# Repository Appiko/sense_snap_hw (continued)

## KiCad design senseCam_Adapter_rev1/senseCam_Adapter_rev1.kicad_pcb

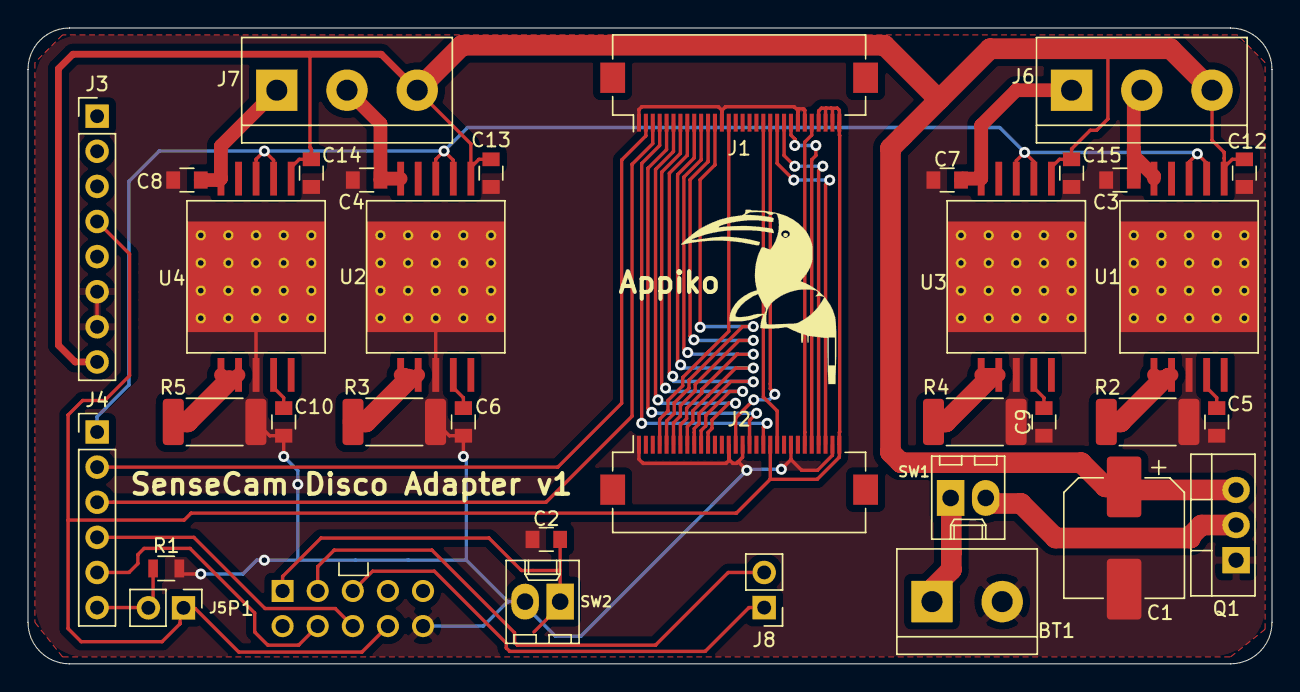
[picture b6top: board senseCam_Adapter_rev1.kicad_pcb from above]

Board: 2 copper layers, 90.0 x 46.0 mm, 36 parts (0 on the bottom side), 42 nets.

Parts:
BT1: LiPo 2s; TerminalBlock_bornier-2_P5.08mm
C1: 100uF; CP_Elec_8x10.5
C2, C12, C13, C14, C15: 100nF; C_0805
C3, C4, C7, C8: 0.47uF; C_0805
C5, C6, C9, C10: 0.1nF; C_0805
J1: Conn_01x30; ArduCam_FPC_30pin_P0.50mm_Horizontal
J2: Conn_01x30; Hirose_FH12-30S-0.5SH_1x30-1MP_P0.50mm_Horizontal
J3: Conn_01x08; PinHeader_1x08_P2.54mm_Vertical
J4: Conn_01x06; PinHeader_1x06_P2.54mm_Vertical
J5: LDR_CONN; Pin_Header_Straight_1x02_Pitch2.54mm
J6, J7: Conn_01x03; TerminalBlock_bornier-3_P5.08mm
J8: Conn_01x02; PinHeader_1x02_P2.54mm_Vertical
P1: CONN_02X05; Berg_5x2Conn
Q1: IRF9540; TO-220-3_Vertical
R1: 10k; R_0805
R2, R3, R4, R5: 0R033; R_2512_6332Metric_Pad1.52x3.35mm_HandSolder
SW1: SW_SPST; Molex_KK-6410-02_02x2.54mm_Straight
SW2: SW_Push; Molex_KK-6410-02_02x2.54mm_Straight
U1, U2, U3, U4: STCS2A; STCS2A_PowerSO-10

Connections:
/3V3: J1.27, J1.28, J1.29, J1.30, J2.20, J2.30, J3.4, J5.1, P1.8
/BUTTON: C2.1, P1.1, SW2.1
/CAM_FLASH: J1.2, J4.2
/CAM_TRIGGER: J1.3, J4.3
/Camera_CLK: J1.19, J2.21
/D4: J1.14, J2.4
/D5: J1.12, J2.5
/D6: J1.11, J2.6
/D7: J1.10, J2.7
/D8: J1.9, J2.8
/D9: J1.8, J2.9
/D10: J1.7, J2.10
/D11: J1.6, J2.11
/DCMI_HSYNC: J1.5, J2.17
/DCMI_NRST: J1.23, J2.26
/DCMI_PIXCK: J1.20, J2.15
/DCMI_PWR_EN: J1.26, J2.25
/DCMI_SCL: J1.21, J2.28
/DCMI_SDA: J1.22, J2.27
/DCMI_VSYNC: J1.4, J2.19
/FLASH_TRIGGER: J4.1, U1.2, U1.3, U2.2, U2.3, U3.2, U3.3, U4.2, U4.3
/FOCUS: J4.5, P1.4
/LDR: J4.6, J5.2, R1.1
/LED1: C3.2, J6.2, U1.5
/LED2: C7.1, J6.1, U3.5
/LED3: C4.2, J7.2, U2.5
/LED4: C8.2, J7.1, U4.5
/SENSE_TRIGGER: J4.4, P1.6
/STM_RX: J8.1, P1.5
/STM_TX: J8.2, P1.3
/VIN: C1.1, C12.1, C13.1, C14.1, C15.1, J3.8, J6.3, J7.3, Q1.3, U1.1, U2.1, U3.1, U4.1
GND: BT1.2, C1.2, C2.2, C3.1, C4.1, C5.1, C6.1, C7.2, C8.1, C9.1, C10.1, C12.2, C13.2, C14.2, C15.2, J1.1, J1.13, J1.24, J1.25, J2.1, J2.14, J2.16, J2.23, J2.29, J3.6, J3.7, P1.10, Q1.1, R1.2, R2.2, R3.2, R4.2, R5.2, SW2.2, U1.8, U1.11, U2.8, U2.11, U3.8, U3.11, U4.8, U4.11
unnamed: BT1.1, SW1.1
unnamed: C5.2, U1.9
unnamed: C6.2, U2.9
unnamed: C9.2, U3.9
unnamed: C10.2, U4.9
unnamed: Q1.2, SW1.2
unnamed: R2.1, U1.6, U1.7
unnamed: R3.1, U2.6, U2.7
unnamed: R4.1, U3.6, U3.7
unnamed: R5.1, U4.6, U4.7

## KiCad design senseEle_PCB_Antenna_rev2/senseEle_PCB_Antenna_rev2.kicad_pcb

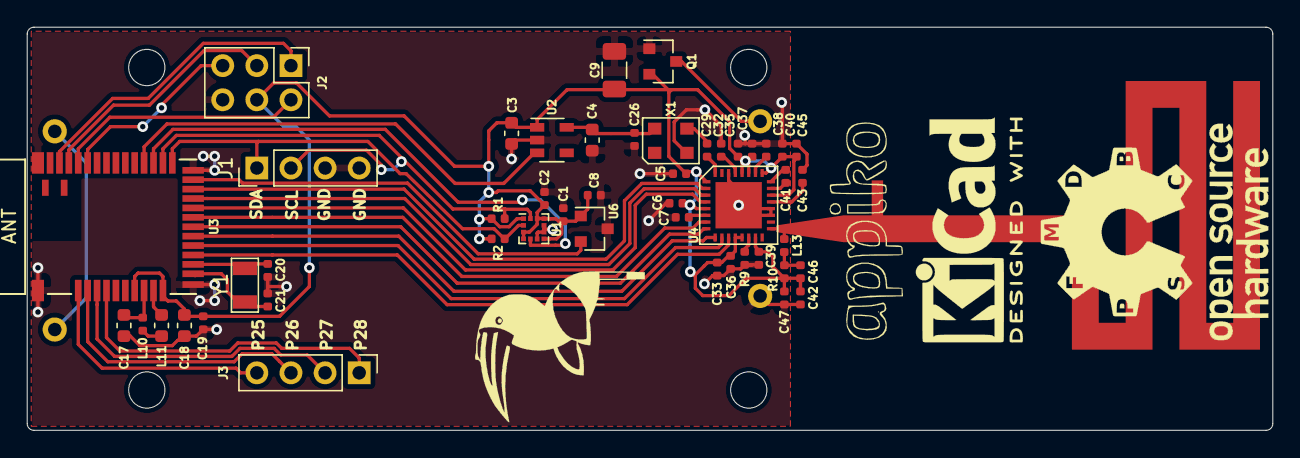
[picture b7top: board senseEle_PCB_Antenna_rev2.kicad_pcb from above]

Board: 2 copper layers, 92.7 x 30.0 mm, 54 parts (1 on the bottom side), 42 nets.

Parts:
AE1: Antenna; DN024_taper
BT1: MP000325
C1, C2, C8, C19, C26: 100nF; C_0402_1005Metric
C3, C4, C17, C18: 1uF; C_0603_1608Metric
C5, C6, C32, C33, C35, C36, C37, C38, C39, C40, C45: 47nF; C_0402_1005Metric
C7: 220nF; C_0402_1005Metric
C9: 22uF; C_1206_3216Metric
C20, C21: 8pF; C_0402_1005Metric
C29: 22pF; C_0402_1005Metric
C41: 1.8nF; C_0402_1005Metric
C42, C43: 10nF; C_0402_1005Metric
C46: 33pF; C_0402_1005Metric
C47: 100pF; C_0402_1005Metric
J1: Conn_01x02; PinHeader_1x04_P2.54mm_Vertical
J2: Conn_02x03_Odd_Even; PinHeader_2x03_P2.54mm_Vertical
J3: Conn_01x04; PinHeader_1x04_P2.54mm_Vertical
L10: 15nH; C_0402_1005Metric
L11: 10uH; C_0603_1608Metric
L13: 10nH; C_0402_1005Metric
MK1, MK2, MK3, MK4: Mounting_Hole; MountingHole_2.7mm_M2.5
Q1: IRLML6401; SOT-23
R1, R2: 10k; C_0402_1005Metric
R9: 56k; C_0402_1005Metric
R10: 10E; C_0402_1005Metric
U1: KXTJ3-1057; LGA-12_2x2mm_P0.5mm
U2: MIC5504-1.8YM5; SOT-23-5
U3: MDBT42Q; mdbt42Q
U4: CC1175; CC1120
U6: SI7201-B-00-FV; SOT-23
X1: TXKTPCSANF-32
Y1: Crystal; Q13FC1350000400_SMD_Crystals

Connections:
/CC1120/1V8: C4.2, C26.2, U2.5, X1.4
/CC1120/CSN: U3.15, U4.11
/CC1120/GPIO0: U3.16, U4.10
/CC1120/GPIO2: U3.20, U4.4
/CC1120/GPIO3: U3.21, U4.3
/CC1120/MISO: U3.17, U4.9
/CC1120/MOSI: U3.19, U4.7
/CC1120/RESET_N: U3.22, U4.2
/CC1120/SCLK: U3.18, U4.8
/CC1120/TCXO_EN: U2.3, U3.28
/nRF_Module/DCC: L11.2, U3.10
/nRF_Module/DEC4: C17.1, L10.1, U3.9
/nRF_Module/HallEffect: U3.23, U6.2
/nRF_Module/INT: U1.5, U3.27
/nRF_Module/RX: J2.2, U3.35
/nRF_Module/SCL: J1.2, R1.2, U1.12, U3.26
/nRF_Module/SDA: J1.1, R2.2, U1.2, U3.25
/nRF_Module/SWDCLK: J2.3, U3.36
/nRF_Module/SWDIO: J2.1, U3.37
/nRF_Module/TX: J2.5, U3.34
/nRF_Module/XL1: C20.1, U3.13, Y1.1
/nRF_Module/XL2: C21.1, U3.14, Y1.2
GND: BT1.2, C1.2, C2.2, C3.1, C4.1, C5.1, C6.1, C7.1, C8.2, C9.2, C17.2, C18.2, C19.2, C20.2, C21.2, C26.1, C32.2, C33.1, C35.2, C36.1, C37.2, C38.2, C39.1, C40.2, C42.1, C43.1, C45.1, C47.1, J1.3, J1.4, J2.6, Q1.1, R9.2, U1.6, U1.8, U1.9, U2.2, U3.1, U3.12, U3.24, U3.39, U4.19, U4.20, U4.30, U4.33, U6.3, X1.2
unnamed: AE1.1, L13.1, U4.17
unnamed: BT1.1, BT1.4
unnamed: BT1.3, Q1.3
unnamed: C7.2, U4.6
unnamed: C29.1, U4.32
unnamed: C29.2, X1.3
unnamed: C32.1, U4.29
unnamed: C38.1, U4.26
unnamed: C41.1, U4.23
unnamed: C41.2, U4.24
unnamed: C43.2, U4.21
unnamed: C46.2, L13.2, R10.1
unnamed: J3.1, U3.5
unnamed: J3.2, U3.4
unnamed: J3.3, U3.3
unnamed: J3.4, U3.2
unnamed: L10.2, L11.1
unnamed: R9.1, U4.14
VDD: C1.1, C2.1, C3.2, C5.2, C6.2, C8.1, C9.1, C18.1, C19.1, C33.2, C35.1, C36.2, C37.1, C39.2, C40.1, C42.2, C45.2, C46.1, C47.2, J2.4, Q1.2, R1.1, R2.1, R10.2, U1.1, U1.3, U1.4, U1.7, U1.10, U1.11, U2.1, U3.8, U3.11, U4.1, U4.5, U4.12, U4.13, U4.15, U4.22, U4.25, U4.27, U4.28, U6.1

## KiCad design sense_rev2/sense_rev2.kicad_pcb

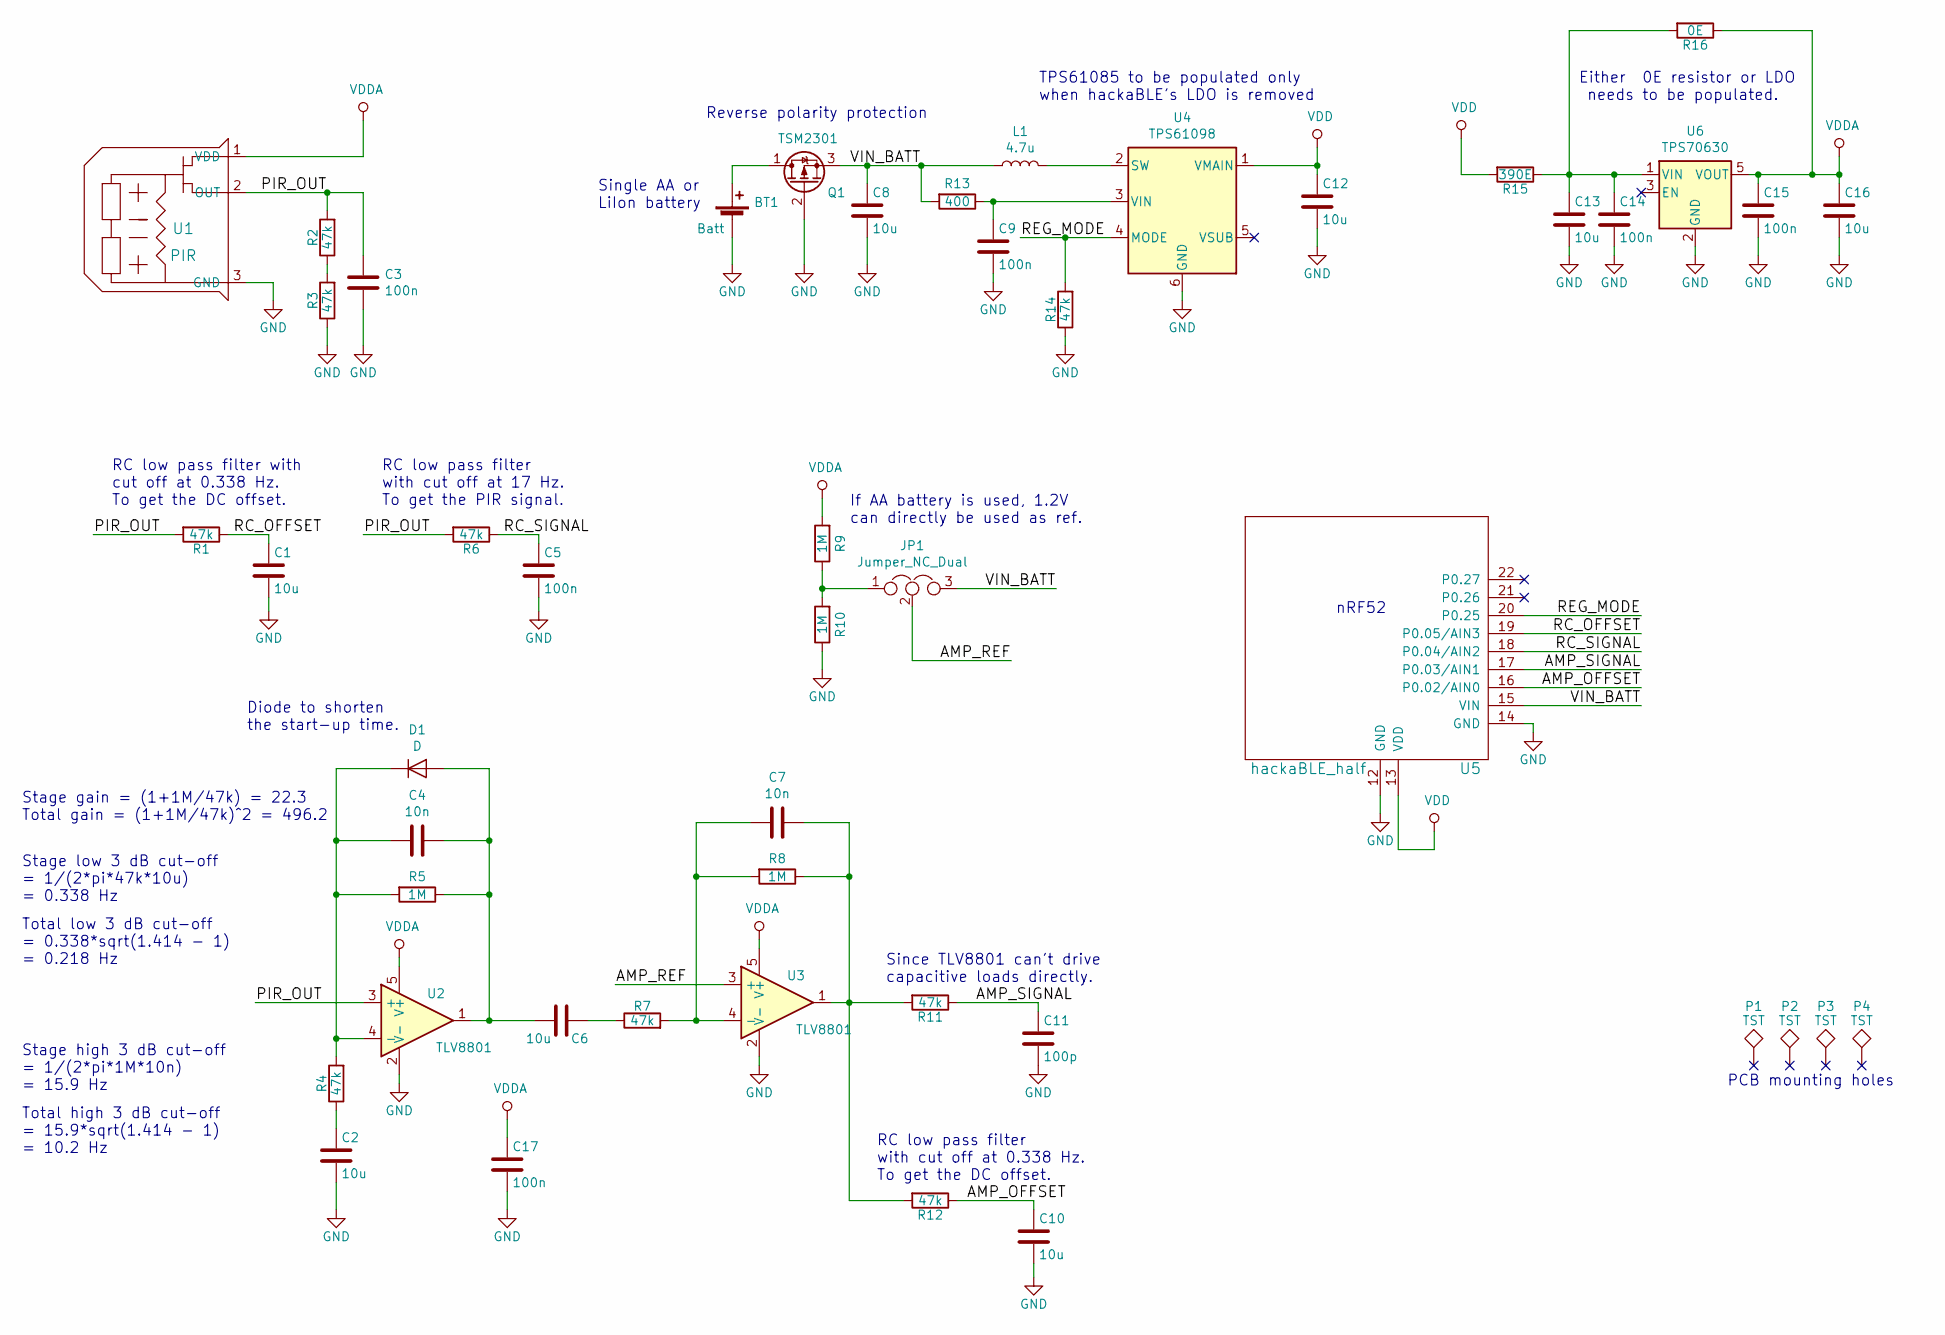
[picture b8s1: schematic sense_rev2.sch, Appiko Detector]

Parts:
BT1: Batt; Pin_Header_Straight_1x02_Pitch2.54mm
C1, C2, C6, C8, C10, C12, C13, C16: 10u; C_0805; Rating >10V
C3, C5: 100n; C_0805
C4, C7: 10n; C_0805
C9, C14, C15, C17: 100n; C_0805; Rating >10V
C11: 100p; C_0805; Rating >10V
D1: D; D_1206
JP1: Jumper_NC_Dual; Pin_Header_Straight_1x03_Pitch1.00mm_SMD_Pin1Left
L1: 4.7u; C_0805
P1, P2, P3, P4: TST; MountingHole_2.2mm_M2_DIN965
Q1: TSM2301; SOT-23; Part Number TSM2301CX
R1, R2, R3, R4, R6, R7, R11, R12, R14: 47k; C_0805
R5, R8, R9, R10: 1M; C_0805
R13: 400; C_0805
R15: 390E; C_0805
R16: 0E; C_0201
U1: PIR; PIR_TO5; Part Number D203B LHi968
U2, U3: TLV8801; SOT-23-5
U4: TPS61098; WSON6_1.5x1.5mm_Pitch0.5mm
U5: hackaBLE_half; hackable_footprint_half
U6: TPS70630; SOT-23-5

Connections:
/AMP_OFFSET: C10.1, R12.1, U5.16 (P0.02/AIN0)
/AMP_REF: JP1.2, U3.3 (+)
/AMP_SIGNAL: C11.1, R11.1, U5.17 (P0.03/AIN1)
/PIR_OUT: C3.1, R1.2, R2.2, R6.2, U1.2 (OUT), U2.3 (+)
/RC_OFFSET: C1.1, R1.1, U5.19 (P0.05/AIN3)
/RC_SIGNAL: C5.1, R6.1, U5.18 (P0.04/AIN2)
/REG_MODE: R14.2, U4.4 (MODE), U5.20 (P0.25)
/VIN_BATT: C8.1, JP1.3, L1.1, Q1.3 (S), R13.2, U5.15 (VIN)
GND: BT1.2 (-), C1.2, C2.2, C3.2, C5.2, C8.2, C9.2, C10.2, C11.2, C12.2, C13.2, C14.2, C15.2, C16.2, C17.2, Q1.2 (G), R3.1, R10.1, R14.1, U1.3 (GND), U2.2 (V-), U3.2 (V-), U4.6 (GND), U5.12 (GND), U5.14 (GND), U6.2 (GND)
unnamed: BT1.1 (+), Q1.1 (D)
unnamed: C2.1, R4.1
unnamed: C4.1, C6.2, D1.2 (A), R5.1, U2.1
unnamed: C4.2, D1.1 (K), R4.2, R5.2, U2.4 (-)
unnamed: C6.1, R7.1
unnamed: C7.1, R8.1, R11.2, R12.2, U3.1
unnamed: C7.2, R7.2, R8.2, U3.4 (-)
unnamed: C9.1, R13.1, U4.3 (VIN)
unnamed: C13.1, C14.1, R15.1, R16.2, U6.1 (VIN)
unnamed: JP1.1, R9.1, R10.2
unnamed: L1.2, U4.2 (SW)
unnamed: R2.1, R3.2
VDD: C12.1, R15.2, U4.1 (VMAIN), U5.13 (VDD)
VDDA: C15.1, C16.1, C17.1, R9.2, R16.1, U1.1 (VDD), U2.5 (V+), U3.5 (V+), U6.5 (VOUT)

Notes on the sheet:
PCB mounting holes
Reverse polarity protection
RC low pass filter with cut off at 17 Hz. To get the PIR signal.
RC low pass filter with cut off at 0.338 Hz. To get the DC offset.
RC low pass filter with cut off at 0.338 Hz. To get the DC offset.
Since TLV8801 can't drive capacitive loads directly.
Diode to shorten the start-up time.
Stage gain = (1+1M/47k) = 22.3 Total gain = (1+1M/47k)^2 = 496.2
Stage low 3 dB cut-off = 1/(2*pi*47k*10u) = 0.338 Hz
Total low 3 dB cut-off = 0.338*sqrt(1.414 - 1) = 0.218 Hz
Stage high 3 dB cut-off = 1/(2*pi*1M*10n) = 15.9 Hz
Total high 3 dB cut-off = 15.9*sqrt(1.414 - 1) = 10.2 Hz
nRF52
TPS61085 to be populated only when hackaBLE's LDO is removed
Either 0E resistor or LDO needs to be populated.
Single AA or LiIon battery
If AA battery is used, 1.2V can directly be used as ref.

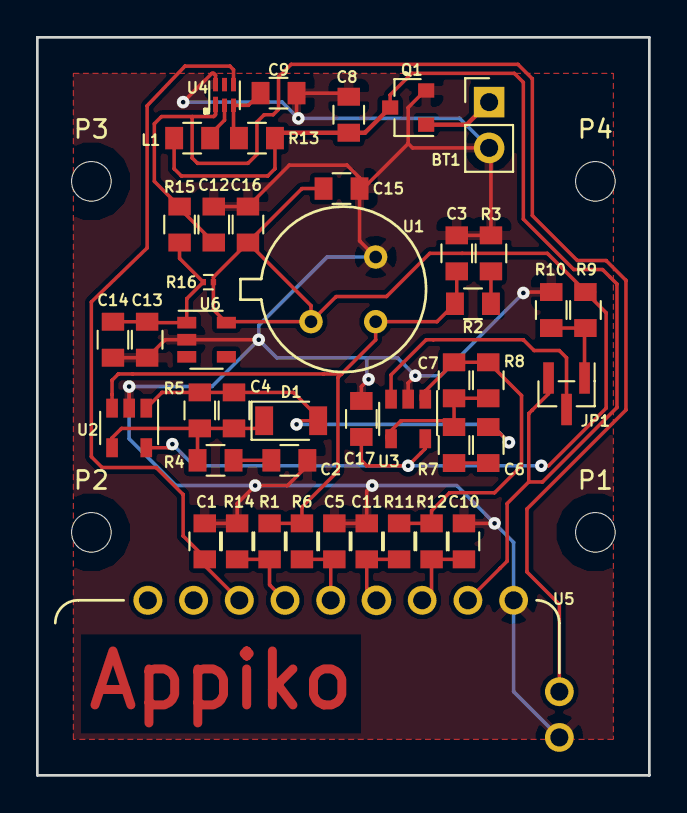
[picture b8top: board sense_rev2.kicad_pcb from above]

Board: 2 copper layers, 34.0 x 41.0 mm, 48 parts (0 on the bottom side), 23 nets.

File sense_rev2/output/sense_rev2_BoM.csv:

Reference,Quantity,Value,Footprint,Datasheet,Part Number,Rating
"U1","1","PIR","detect_trigger:PIR_TO5","http://www.micropik.com/PDF/D203B-e.pdf http://www.perkinelmer.com/PDFs/Downloads/DTS_LHi968_PYD1398.pdf","D203B LHi968",""
"R15","1","390E","Capacitors_SMD:C_0805","","",""
"R6;R1;R2;R3;R4;R7;R12;R11;R14","9","47k","Capacitors_SMD:C_0805","","",""
"C5;C3","2","100n","Capacitors_SMD:C_0805","","",""
"R13","1","400E","Capacitors_SMD:C_0805","","",""
"C1;C8;C2;C6;C10;C16;C13;C12","8","10u","Capacitors_SMD:C_0805","","",">10V"
"U5","1","hackaBLE_half","detect_trigger:hackable_footprint_half","https://github.com/electronut/ElectronutLabs-hackaBLE","",""
"Q1","1","TSM2301","TO_SOT_Packages_SMD:SOT-23","http://www.farnell.com/datasheets/2044652.pdf","TSM2301CX",""
"P1;P2;P3;P4","4","TST","Mounting_Holes:MountingHole_2.2mm_M2_DIN965","","",""
"JP1","1","Jumper_NC_Dual","Pin_Headers:Pin_Header_Straight_1x03_Pitch1.00mm_SMD_Pin1Left","","",""
"BT1","1","Batt","Pin_Headers:Pin_Header_Straight_1x02_Pitch2.54mm","","",""
"U2;U3","2","TLV8801","TO_SOT_Packages_SMD:SOT-23-5","","",""
"U6","1","TPS70630","TO_SOT_Packages_SMD:SOT-23-5","http://www.ti.com/lit/ds/symlink/tps706.pdf","",""
"U4","1","TPS61098","Housings_SON:WSON6_1.5x1.5mm_Pitch0.5mm","http://www.ti.com/lit/ds/symlink/tps610985.pdf","",""
"R5;R8;R9;R10","4","1M","Capacitors_SMD:C_0805","","",""
"C4;C7","2","10n","Capacitors_SMD:C_0805","","",""
"R16","1","0E","Capacitors_SMD:C_0201","","",""
"L1","1","4.7u","Capacitors_SMD:C_0805","","",""
"C9;C15;C14;C17","4","100n","Capacitors_SMD:C_0805","","",">10V"
"C11","1","100p","Capacitors_SMD:C_0805","","",">10V"
"D1","1","LL4148","Diodes_SMD:D_1206","https://www.fairchildsemi.com/datasheets/LL/LL4148.pdf","",""
